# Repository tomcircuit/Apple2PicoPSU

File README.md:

# Apple 2 Pico PSU
12V Input Power Supply retrofit for vintage Apple //e  computers

Many vintage Apple(R) ][ and // series computers suffer from power supply failure. These computers were fitted with switching power supplies (SMPS) that, for the time, were notable for their lightweight, quiet, and efficient characteristics. Time, however, has not been kind to these supplies, which are vulnerable to aging. There is no drop-in replacment unit, so most enthusiasts are forced to either repair their supply or replace with a modern retrofit. This project is of the latter type, and my motivation was when my Apple //e computer's power supply emitted the dreaded "magic smoke" (AFTER a complete re-cap, mind you) and resisted my efforts at repair.

First and foremost, this project is insprired by the "PicoRC" project family by DekuNukem, currently found here: https://github.com/dekuNukem/PicoRC
Note that that project is licensed under MIT License terms:

```
MIT License

Copyright (c) 2022 dekuNukem

Permission is hereby granted, free of charge, to any person obtaining a copy
of this software and associated documentation files (the "Software"), to deal
in the Software without restriction, including without limitation the rights
to use, copy, modify, merge, publish, distribute, sublicense, and/or sell
copies of the Software, and to permit persons to whom the Software is
furnished to do so, subject to the following conditions:

The above copyright notice and this permission notice shall be included in all
copies or substantial portions of the Software.

THE SOFTWARE IS PROVIDED "AS IS", WITHOUT WARRANTY OF ANY KIND, EXPRESS OR
IMPLIED, INCLUDING BUT NOT LIMITED TO THE WARRANTIES OF MERCHANTABILITY,
FITNESS FOR A PARTICULAR PURPOSE AND NONINFRINGEMENT. IN NO EVENT SHALL THE
AUTHORS OR COPYRIGHT HOLDERS BE LIABLE FOR ANY CLAIM, DAMAGES OR OTHER
LIABILITY, WHETHER IN AN ACTION OF CONTRACT, TORT OR OTHERWISE, ARISING FROM,
OUT OF OR IN CONNECTION WITH THE SOFTWARE OR THE USE OR OTHER DEALINGS IN THE
SOFTWARE.
```

I did not directly modify the Eagle PCB nor Schematic files, and this work is my own, but I do feel that it is only proper to give DekuNukem attribution for the inspiration for this project. I license my project under CC-BY-SA-4.0 which can accept an MIT License as an "inbound license", in the event that my work is determined to be derivative after all.

There, that out of the way...

It's a **Great Idea** to move the AC-DC converter to the **outside of the Apple's case** for many reasons some of which are: it's heavy, it generates heat, and it allows for the possiblity to scale the PSU Wattage as required by the peripheral load. Any 12VDC supply with sufficient wattage and mating connector can be used, so that only 12VDC goes into the computer via the rear panel.

The **PicoPSU** units that are aimed at Small Form Factor (SFF) PC's are an ideal solution to convert the incoming 12VDC to +5V, +15V and -12V. These are available from many sources, in varying Wattages. I chose an 80W type for my own use, which should be more than sufficient. All that is missing is the -5V which is (questionably) required by the Apple motherboard.

Like the PicoRC for the Apple, my Apple2PicoPSU provides a power switch, a 24-pin Molex connector for the PicoPSU, fuses for the +5V and +12V voltage rails, and a -5V regulator for the 'missing' rail. I adoped a similar "PCB-welded" construction of a back panel and circuit board, because it seemed like a very convenient way to satisfy the mechanical aspects.

Improvements over the original PicoRC for the Apple are the following:
* power switch suitable for switching the low-current PicoPSU enable
* the 7905 voltage regulator would benefit from some sort of heatsinking
* LED for each voltage rail, visible from the outside of the case
* copper tracks sized sufficiently for the anticipated current demand

It is this last point in particular that really drove me to re-engineer this concept; I am quite skeptical of the copper track widths used in the original. I have sized the copper tracks for at least 8A on the 5V rail, and 4A on the 12V rail, assuming 1oz Cu and a modest 15C temperature rise over ambient.

My project was executed in the very capable open-source and "completely free" KiCad 10.0 which is well supported by the usual Operating Systems suspects...

Complete project writeup, including assembly instructions, can be found on Hackaday
https://hackaday.io/project/205643-a-modern-psu-for-my-apple-e

tomcircuit
01-MAY-2026

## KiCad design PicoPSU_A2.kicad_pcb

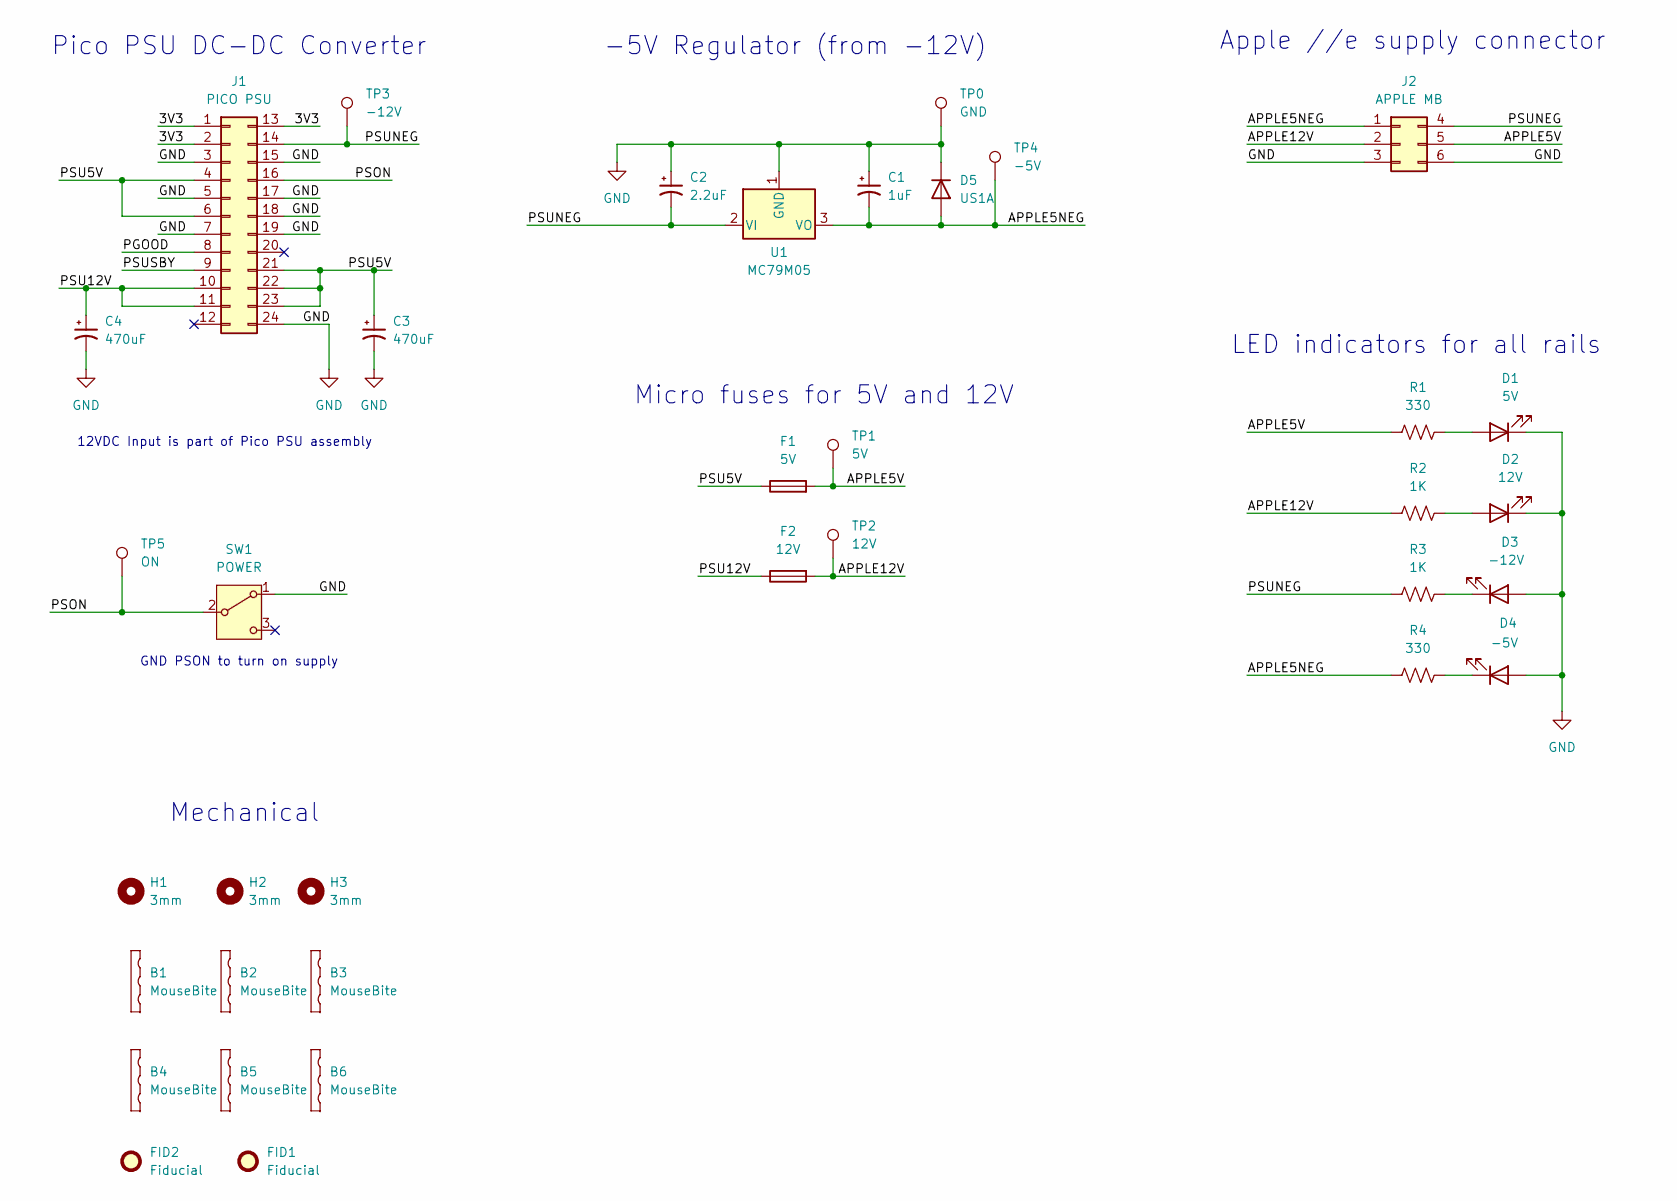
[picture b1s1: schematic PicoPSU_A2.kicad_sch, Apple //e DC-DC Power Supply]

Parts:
B1, B2, B3, B4, B5, B6: MouseBite; MouseBite-Part_2.0x2.0mm_inset_D0.5mm_P0.85mm_5h
C1: 1uF; CP_Radial_D5.0mm_P2.00mm
C2: 2.2uF; CP_Radial_D5.0mm_P2.00mm
C3, C4: 470uF; CP_Radial_D10.0mm_P5.00mm
D1: 5V; LED_D3.0mm
D2: 12V; LED_D3.0mm
D3: -12V; LED_D3.0mm
D4: -5V; LED_D3.0mm
D5: US1A; D_SMA
F1: 5V; Fuseholder_Blade_Mini_Keystone_3568
F2: 12V; Fuseholder_Blade_Mini_Keystone_3568
FID1: Fiducial; KiCad-Logo2_6mm_SilkScreen
FID2: Fiducial; Symbol_CC-ShareAlike_CopperTop_Small
H1, H2, H3: 3mm; MountingHole_3mm
J1: PICO PSU; Molex_Mini-Fit_Jr_5569-24A2_2x12_P4.20mm_Horizontal; MPN 0039299243
J2: APPLE MB; Molex_Mini-Fit_Jr_5566-06A_2x03_P4.20mm_Vertical; MPN 0039288060
R1, R4: 330; R_0805_2012Metric
R2, R3: 1K; R_0805_2012Metric
SW1: POWER; PN12SHSA03QE; MPN PN12SHSA03QE
TP0: GND; TestPoint_Pad_D2.0mm
TP1: 5V; TestPoint_Pad_D2.0mm
TP2: 12V; TestPoint_Pad_D2.0mm
TP3: -12V; TestPoint_Pad_D2.0mm
TP4: -5V; TestPoint_Pad_D2.0mm
TP5: ON; TestPoint_Pad_D2.0mm
U1: MC79M05; TO-252-2; MPN MC79M05CDTRKG

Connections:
/3V3: J1.1, J1.2, J1.13
/APPLE5NEG: C1.2, D5.2 (A), J2.1, R4.1, TP4.1 (1_1), U1.3 (VO)
/APPLE5V: F1.2, J2.5, R1.1, TP1.1 (1_1)
/APPLE12V: F2.2, J2.2, R2.1, TP2.1 (1_1)
/PGOOD: J1.8
/PSON: J1.16, SW1.2 (B), TP5.1 (1_1)
/PSU5V: C3.1, F1.1, J1.4, J1.6, J1.21, J1.22, J1.23
/PSU12V: C4.1, F2.1, J1.10, J1.11
/PSUNEG: C2.2, J1.14, J2.4, R3.1, TP3.1 (1_1), U1.2 (VI)
/PSUSBY: J1.9
GND: C1.1, C2.1, C3.2, C4.2, D1.1 (K), D2.1 (K), D3.2 (A), D4.2 (A), D5.1 (K), J1.3, J1.5, J1.7, J1.15, J1.17, J1.18, J1.19, J1.24, J2.3, J2.6, SW1.1 (A), TP0.1 (1_1), U1.1 (GND)
unnamed: D1.2 (A), R1.2
unnamed: D2.2 (A), R2.2
unnamed: D3.1 (K), R3.2
unnamed: D4.1 (K), R4.2

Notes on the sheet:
GND PSON to turn on supply
12VDC Input is part of Pico PSU assembly
Micro fuses for 5V and 12V
Mechanical
-5V Regulator (from -12V)
Pico PSU DC-DC Converter
LED indicators for all rails
Apple //e supply connector

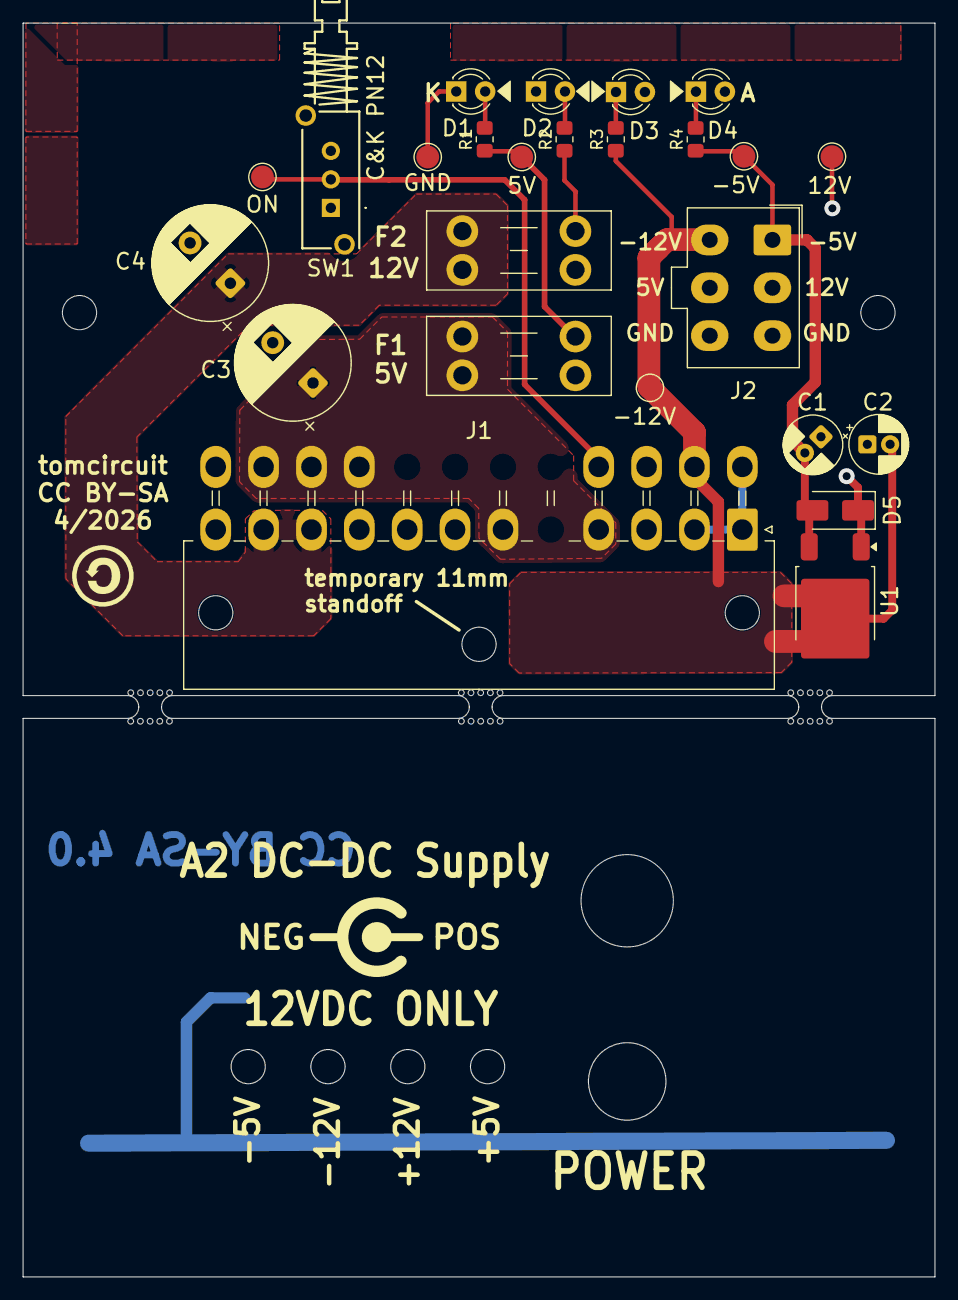
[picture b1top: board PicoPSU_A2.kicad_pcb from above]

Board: 2 copper layers, 79.9 x 109.9 mm, 36 parts (1 on the bottom side), 13 nets.

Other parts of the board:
H1#2: 3mm; MountingHole_3mm

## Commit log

2026-05-02 Create LICENSE.txt
    Added CC-BY-SA-4.0 license terms
2026-05-02 1v1 Commit
    Updated readme and license files.
    Added KiCAD project files
    Added Fabrication files
    Added Plot files
2026-05-02 Initial commit of 1v1
    Updated readme
    Added KiCad project files
    Added Fabrication files
    Added Plot files
2026-05-02 Delete Fabrication/Fabrication_1v0.zip
    removed 1v0 fabrication archive
2026-05-02 Delete Plots/Plots 1v0 directory
    removed 1v0 plot directory
2026-05-02 Update README.md
    Clarified which project is licensed under MIT terms
2026-05-02 Update README.md
    added reference to 7905 heatsinking
2026-05-02 Update README.md
    added link to Hackaday page

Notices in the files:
PicoPSU_A2.kicad_pcb:
this derivative distributed under CC BY-SA 4.0
which is compliant with inbound MIT license
